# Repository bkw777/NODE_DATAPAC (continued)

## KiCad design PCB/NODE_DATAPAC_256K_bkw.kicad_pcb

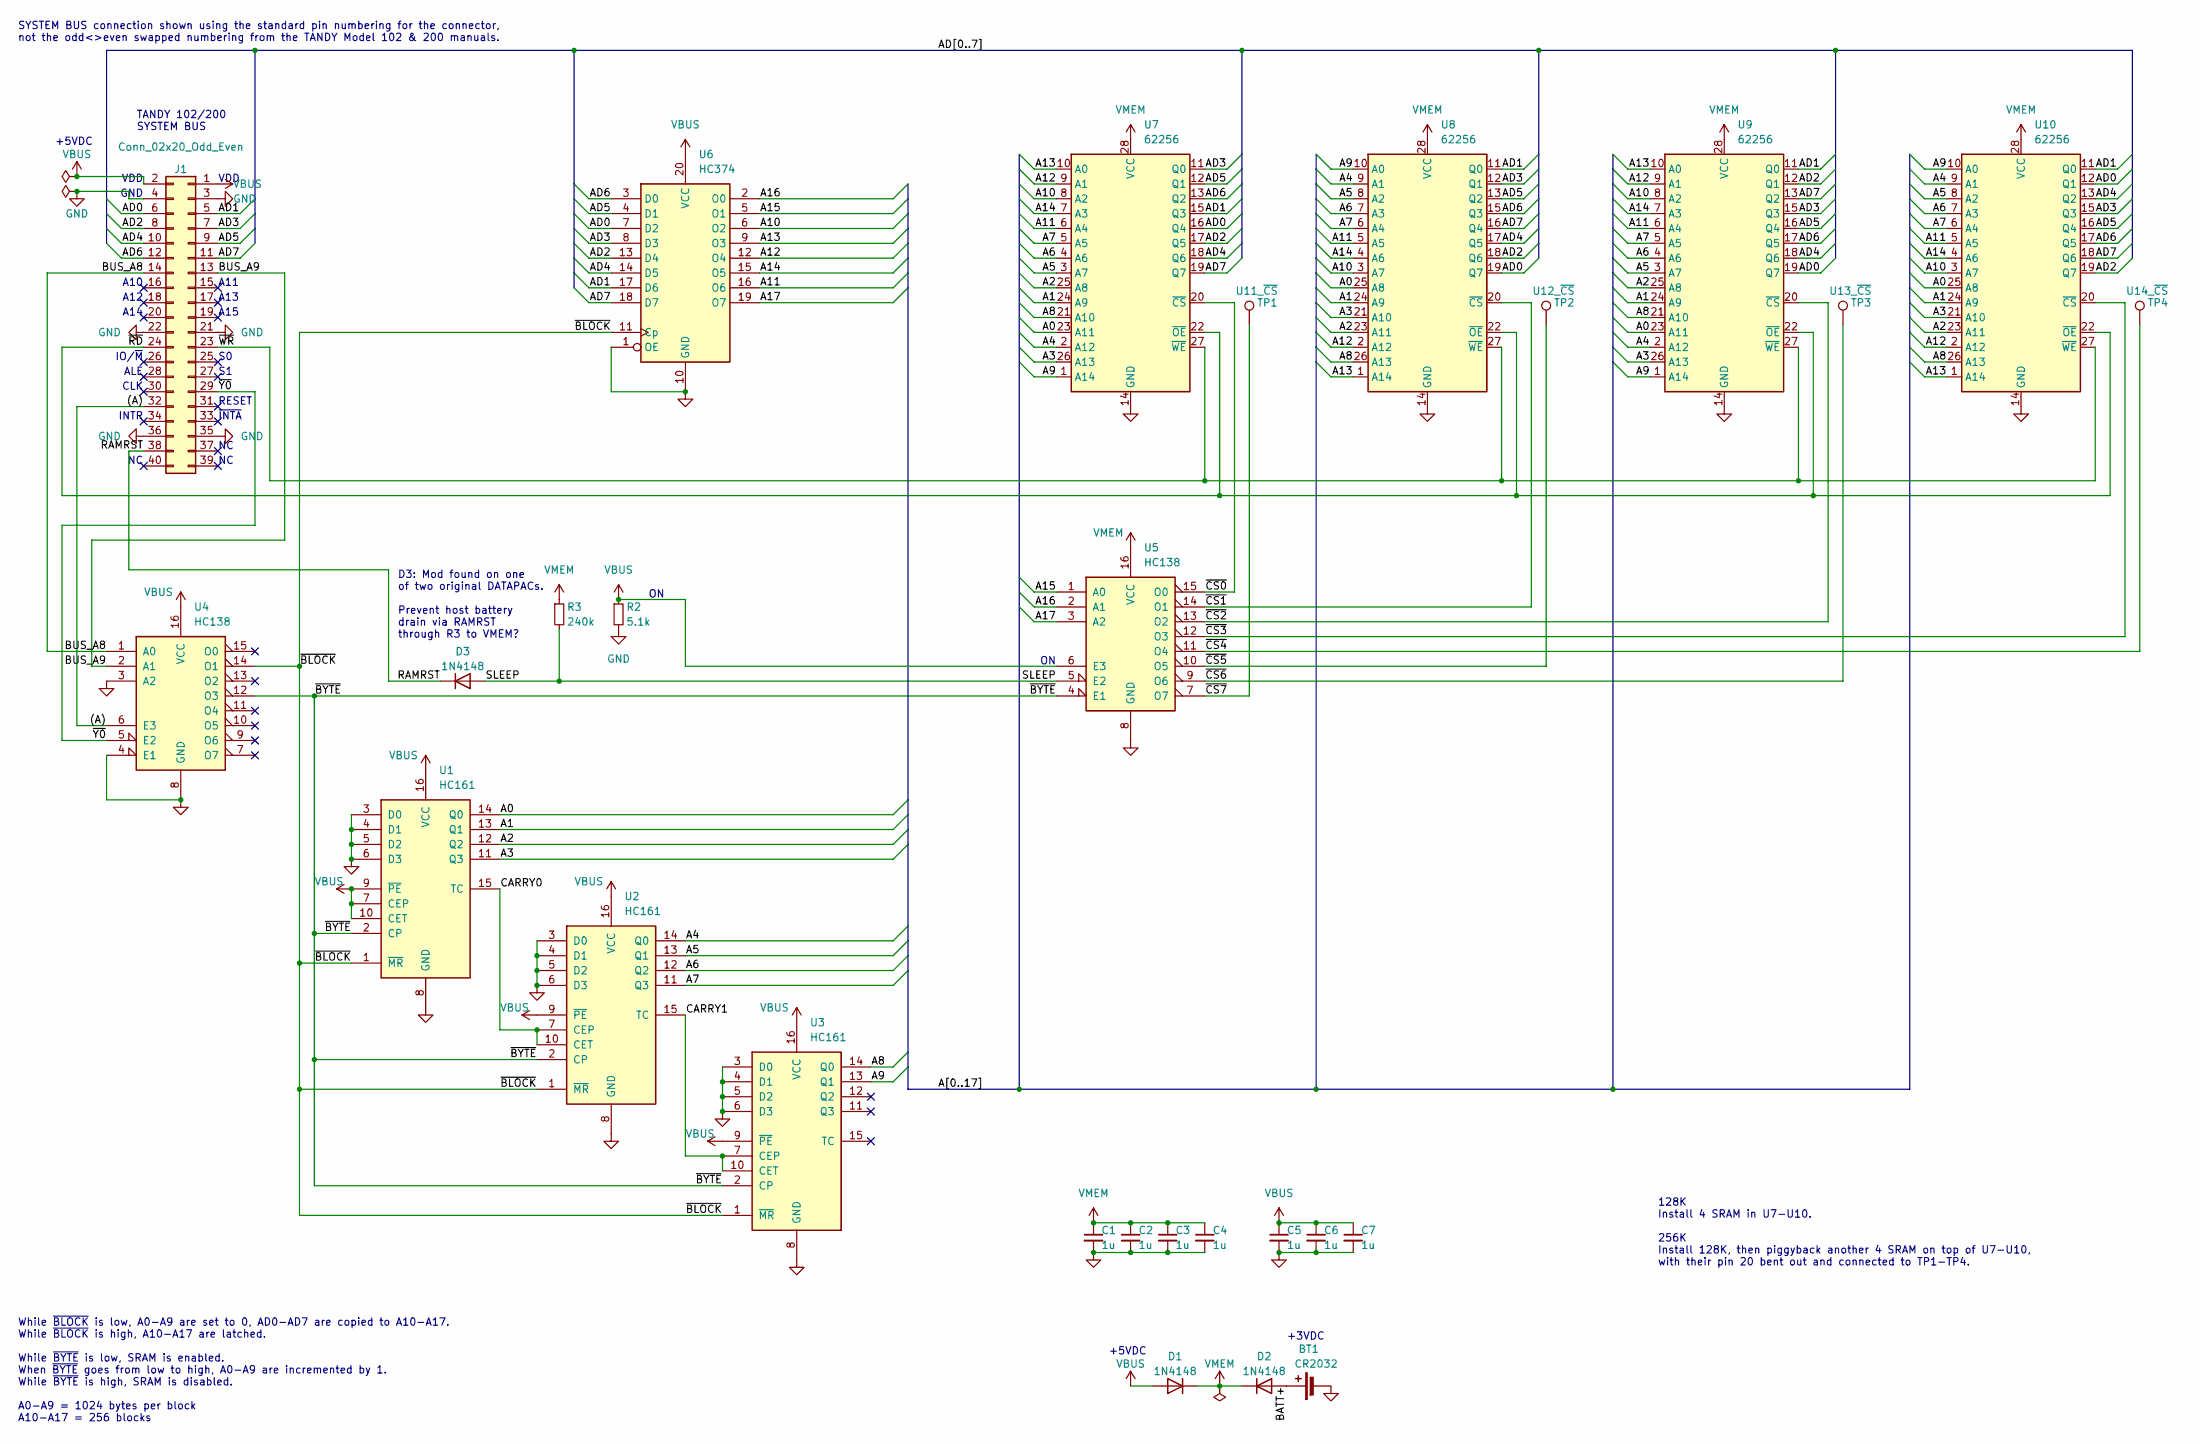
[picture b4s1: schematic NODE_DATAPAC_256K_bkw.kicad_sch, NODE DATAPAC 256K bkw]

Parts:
BT1: CR2032; BH-25x-x
C1, C2, C3, C4, C5, C6, C7: 1u; C_cer_tht_p2.5
D1, D2, D3: 1N4148; D_DO-35_SOD27_P10.16mm_Horizontal
J1: Conn_02x20_Odd_Even; IDC_to_board_2x20
R2: 5.1k; R_Axial_DIN0207_L6.3mm_D2.5mm_P10.16mm_Horizontal
R3: 240k; R_Axial_DIN0207_L6.3mm_D2.5mm_P10.16mm_Horizontal
TP1: U11_~{CS}; TP_THT
TP2: U12_~{CS}; TP_THT
TP3: U13_~{CS}; TP_THT
TP4: U14_~{CS}; TP_THT
U1, U2, U3: HC161; DIP-16_W7.62mm
U4, U5: HC138; DIP-16_W7.62mm
U6: HC374; DIP-20_W7.62mm
U7, U8, U9, U10: 62256; DIP-28_W15.24mm

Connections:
/(A): J1.32, U4.6 (E3)
/A0: U1.14 (Q0), U7.23 (A11), U8.25 (A8), U9.23 (A11), U10.25 (A8)
/A1: U1.13 (Q1), U7.24 (A9), U8.24 (A9), U9.24 (A9), U10.24 (A9)
/A2: U1.12 (Q2), U7.25 (A8), U8.23 (A11), U9.25 (A8), U10.23 (A11)
/A3: U1.11 (Q3), U7.26 (A13), U8.21 (A10), U9.26 (A13), U10.21 (A10)
/A4: U2.14 (Q0), U7.2 (A12), U8.9 (A1), U9.2 (A12), U10.9 (A1)
/A5: U2.13 (Q1), U7.3 (A7), U8.8 (A2), U9.3 (A7), U10.8 (A2)
/A6: U2.12 (Q2), U7.4 (A6), U8.7 (A3), U9.4 (A6), U10.7 (A3)
/A7: U2.11 (Q3), U7.5 (A5), U8.6 (A4), U9.5 (A5), U10.6 (A4)
/A8: U3.14 (Q0), U7.21 (A10), U8.26 (A13), U9.21 (A10), U10.26 (A13)
/A9: U3.13 (Q1), U7.1 (A14), U8.10 (A0), U9.1 (A14), U10.10 (A0)
/A10: U6.6 (O2), U7.8 (A2), U8.3 (A7), U9.8 (A2), U10.3 (A7)
/A11: U6.16 (O6), U7.6 (A4), U8.5 (A5), U9.6 (A4), U10.5 (A5)
/A12: U6.12 (O4), U7.9 (A1), U8.2 (A12), U9.9 (A1), U10.2 (A12)
/A13: U6.9 (O3), U7.10 (A0), U8.1 (A14), U9.10 (A0), U10.1 (A14)
/A14: U6.15 (O5), U7.7 (A3), U8.4 (A6), U9.7 (A3), U10.4 (A6)
/A15: U5.1 (A0), U6.5 (O1)
/A16: U5.2 (A1), U6.2 (O0)
/A17: U5.3 (A2), U6.19 (O7)
/AD0: J1.6, U6.7 (D2), U7.16 (Q4), U8.19 (Q7), U9.19 (Q7), U10.12 (Q1)
/AD1: J1.5, U6.17 (D6), U7.15 (Q3), U8.11 (Q0), U9.11 (Q0), U10.11 (Q0)
/AD2: J1.8, U6.13 (D4), U7.17 (Q5), U8.18 (Q6), U9.12 (Q1), U10.19 (Q7)
/AD3: J1.7, U6.8 (D3), U7.11 (Q0), U8.12 (Q1), U9.15 (Q3), U10.15 (Q3)
/AD4: J1.10, U6.14 (D5), U7.18 (Q6), U8.17 (Q5), U9.18 (Q6), U10.13 (Q2)
/AD5: J1.9, U6.4 (D1), U7.12 (Q1), U8.13 (Q2), U9.16 (Q4), U10.16 (Q4)
/AD6: J1.12, U6.3 (D0), U7.13 (Q2), U8.15 (Q3), U9.17 (Q5), U10.17 (Q5)
/AD7: J1.11, U6.18 (D7), U7.19 (Q7), U8.16 (Q4), U9.13 (Q2), U10.18 (Q6)
/BATT+: BT1.1 (+), D2.2 (A)
/BUS_A8: J1.14, U4.1 (A0)
/BUS_A9: J1.13, U4.2 (A1)
/CARRY0: U1.15 (TC), U2.7 (CEP), U2.10 (CET)
/CARRY1: U2.15 (TC), U3.7 (CEP), U3.10 (CET)
/RAMRST: D3.1 (K), J1.38
/SLEEP: D3.2 (A), R3.2, U5.5 (E2)
/~BLOCK: U1.1 (~MR), U2.1 (~MR), U3.1 (~MR), U4.14 (O1), U6.11 (Cp)
/~BYTE: U1.2 (CP), U2.2 (CP), U3.2 (CP), U4.12 (O3), U5.4 (E1)
/~CS0: U5.15 (O0), U7.20 (~CS)
/~CS1: U5.14 (O1), U8.20 (~CS)
/~CS2: U5.13 (O2), U9.20 (~CS)
/~CS3: U5.12 (O3), U10.20 (~CS)
/~CS4: TP4.1, U5.11 (O4)
/~CS5: TP2.1, U5.10 (O5)
/~CS6: TP3.1, U5.9 (O6)
/~CS7: TP1.1, U5.7 (O7)
/~RD: J1.24, U7.22 (~OE), U8.22 (~OE), U9.22 (~OE), U10.22 (~OE)
/~WR: J1.23, U7.27 (~WE), U8.27 (~WE), U9.27 (~WE), U10.27 (~WE)
/~Y0: J1.29, U4.5 (E2)
GND: BT1.2 (-), C1.2, C2.2, C3.2, C4.2, C5.2, C6.2, C7.2, J1.3, J1.4, J1.21, J1.22, J1.35, J1.36, R2.2, U1.3 (D0), U1.4 (D1), U1.5 (D2), U1.6 (D3), U1.8 (GND), U2.3 (D0), U2.4 (D1), U2.5 (D2), U2.6 (D3), U2.8 (GND), U3.3 (D0), U3.4 (D1), U3.5 (D2), U3.6 (D3), U3.8 (GND), U4.3 (A2), U4.4 (E1), U4.8 (GND), U5.8 (GND), U6.1 (OE), U6.10 (GND), U7.14 (GND), U8.14 (GND), U9.14 (GND), U10.14 (GND); also elsewhere on the board
VBUS: C5.1, C6.1, C7.1, D1.2 (A), J1.1, J1.2, R2.1, U1.7 (CEP), U1.9 (~PE), U1.10 (CET), U1.16 (VCC), U2.9 (~PE), U2.16 (VCC), U3.9 (~PE), U3.16 (VCC), U4.16 (VCC), U5.6 (E3), U6.20 (VCC)
VMEM: C1.1, C2.1, C3.1, C4.1, D1.1 (K), D2.1 (K), R3.1, U5.16 (VCC), U7.28 (VCC), U8.28 (VCC), U9.28 (VCC), U10.28 (VCC)

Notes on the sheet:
SYSTEM BUS connection shown using the standard pin numbering for the connector, not the odd<>even swapped numbering from the TANDY Model 102 & 200 manuals.
TANDY 102/200 SYSTEM BUS
+5VDC
A15
INTR
A14
ALE
~{INTA}
CLK
GND
IO/~{M}
D3: Mod found on one of two original DATAPACs. Prevent host battery drain via RAMRST through R3 to VMEM?
VDD
A10
RESET
+3VDC
While ~{BLOCK} is low, A0-A9 are set to 0, AD0-AD7 are copied to A10-A17. While ~{BLOCK} is high, A10-A17 are latched. While ~{BYTE} is low, SRAM is enabled. When ~{BYTE} goes from low to high, A0-A9 are incremented by 1. While ~{BYTE} is high, SRAM is disabled. A0-A9 = 1024 bytes per block A10-A17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
A11
128K Install 4 SRAM in U7-U10. 256K Install 128K, then piggyback another 4 SRAM on top of U7-U10, with their pin 20 bent out and connected to TP1-TP4.
A13
A12

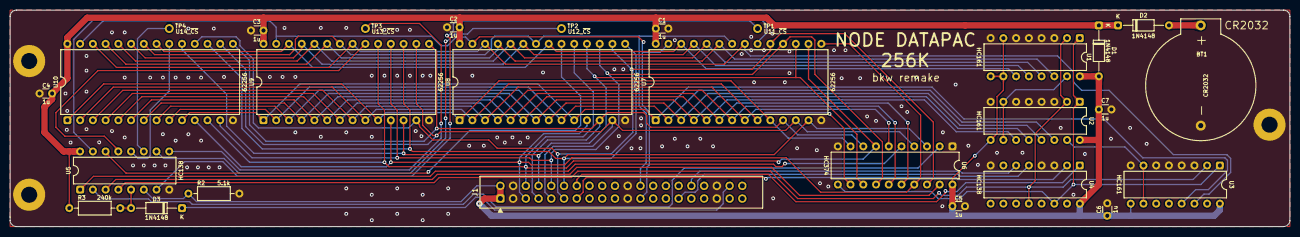
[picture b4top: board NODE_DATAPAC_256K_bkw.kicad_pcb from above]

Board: 2 copper layers, 255.3 x 43.2 mm, 31 parts (0 on the bottom side), 50 nets.

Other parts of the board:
H1, H2, H3: MountHole; MountingHole_3.2mm_M3_Pad

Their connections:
GND: H1.1, H2.1, H3.1; also elsewhere on the board

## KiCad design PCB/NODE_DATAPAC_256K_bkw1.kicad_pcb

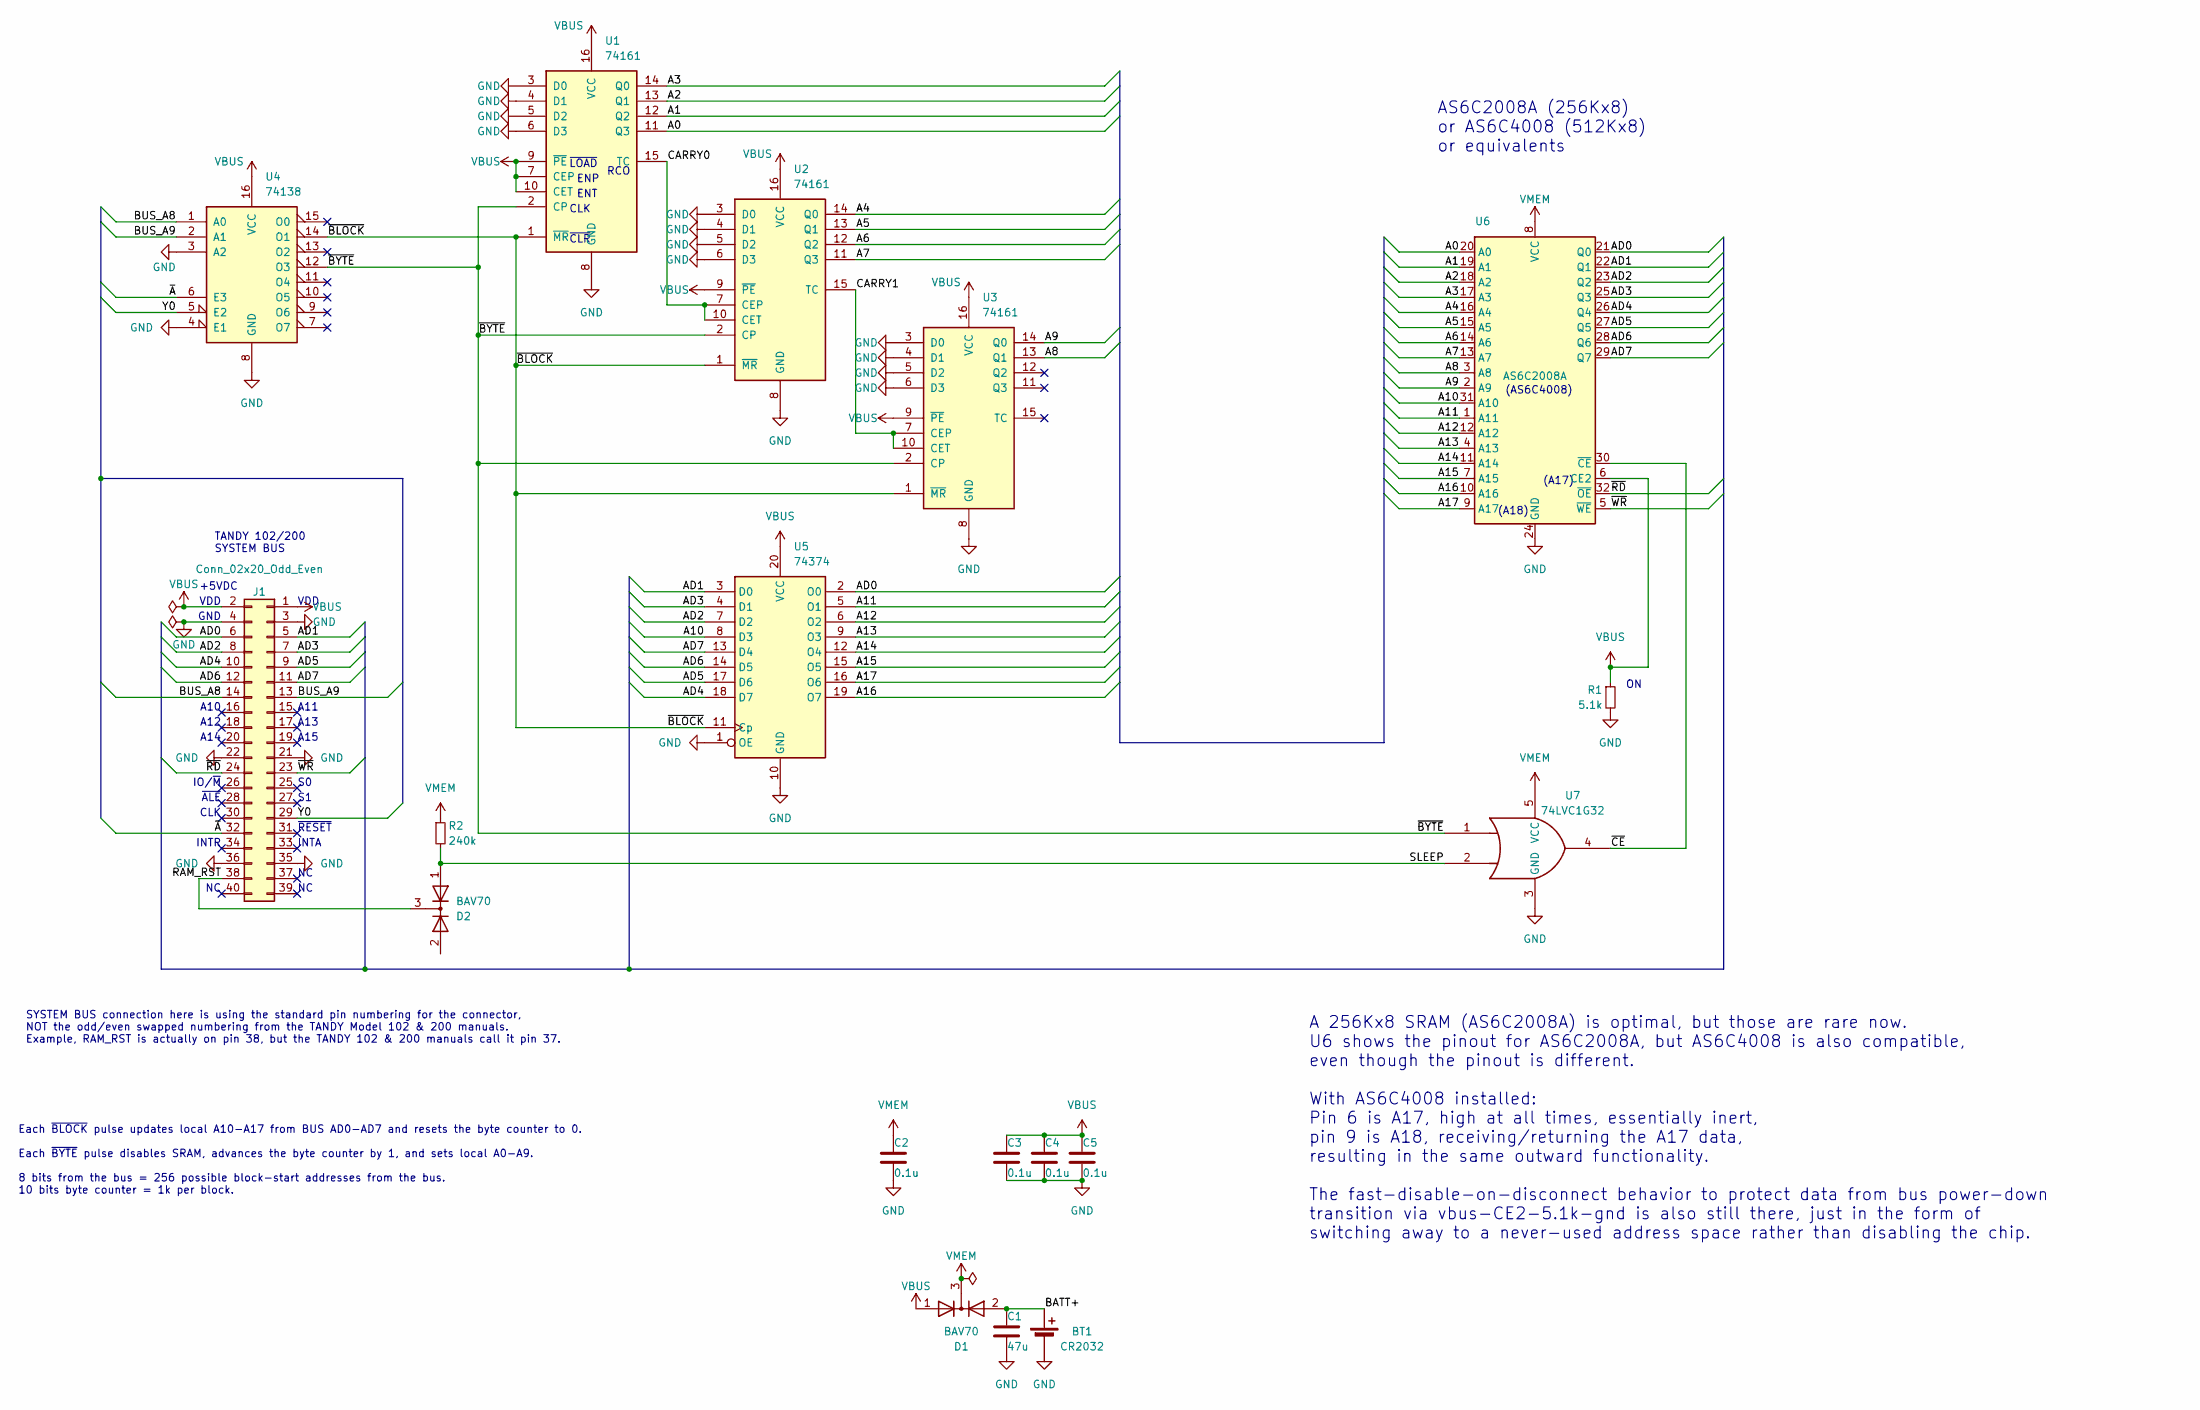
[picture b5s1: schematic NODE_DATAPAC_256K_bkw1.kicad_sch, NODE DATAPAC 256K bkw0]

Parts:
BT1: CR2032; BatteryHolder_Keystone_3034_1x20mm
C1: 47u; C_1206
C2, C3, C4, C5: 0.1u; C_0805
D1, D2: BAV70; SOT-23
J1: Conn_02x20_Odd_Even; IDC-Header_2x20_P2.54mm_Vertical
R1: 5.1k; R_0805
R2: 240k; R_0805
U1, U2, U3: 74161; TSSOP-16
U4: 74138; TSSOP-16
U5: 74374; TSSOP-20
U6: AS6C2008A; TSOP32-dual
U7: 74LVC1G32; SOT-353_SC-70-5

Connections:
/A0: U1.11 (Q3), U6.20 (A0)
/A1: U1.12 (Q2), U6.19 (A1)
/A2: U1.13 (Q1), U6.18 (A2)
/A3: U1.14 (Q0), U6.17 (A3)
/A4: U2.14 (Q0), U6.16 (A4)
/A5: U2.13 (Q1), U6.15 (A5)
/A6: U2.12 (Q2), U6.14 (A6)
/A7: U2.11 (Q3), U6.13 (A7)
/A8: U3.13 (Q1), U6.3 (A8)
/A9: U3.14 (Q0), U6.2 (A9)
/A10: U5.8 (D3), U6.31 (A10)
/A11: U5.5 (O1), U6.1 (A11)
/A12: U5.6 (O2), U6.12 (A12)
/A13: U5.9 (O3), U6.4 (A13)
/A14: U5.12 (O4), U6.11 (A14)
/A15: U5.15 (O5), U6.7 (A15)
/A16: U5.19 (O7), U6.10 (A16)
/A17: U5.16 (O6), U6.9 (A17)
/AD0: J1.6, U5.2 (O0), U6.21 (Q0)
/AD1: J1.5, U5.3 (D0), U6.22 (Q1)
/AD2: J1.8, U5.7 (D2), U6.23 (Q2)
/AD3: J1.7, U5.4 (D1), U6.25 (Q3)
/AD4: J1.10, U5.18 (D7), U6.26 (Q4)
/AD5: J1.9, U5.17 (D6), U6.27 (Q5)
/AD6: J1.12, U5.14 (D5), U6.28 (Q6)
/AD7: J1.11, U5.13 (D4), U6.29 (Q7)
/BATT+: BT1.1 (+), C1.1, D1.2 (A)
/BUS_A8: J1.14, U4.1 (A0)
/BUS_A9: J1.13, U4.2 (A1)
/CARRY0: U1.15 (TC), U2.7 (CEP), U2.10 (CET)
/CARRY1: U2.15 (TC), U3.7 (CEP), U3.10 (CET)
/RAM_RST: D2.3 (K), J1.38
/SLEEP: D2.1 (A), R2.2, U7.2
/Y0: J1.29, U4.5 (E2)
/~A: J1.32, U4.6 (E3)
/~BLOCK: U1.1 (~MR), U2.1 (~MR), U3.1 (~MR), U4.14 (O1), U5.11 (Cp)
/~BYTE: U1.2 (CP), U2.2 (CP), U3.2 (CP), U4.12 (O3), U7.1
/~CE: U6.30 (~CE), U7.4
/~RD: J1.24, U6.32 (~OE)
/~WR: J1.23, U6.5 (~WE)
GND: BT1.2 (-), C1.2, C2.2, C3.2, C4.2, C5.2, J1.3, J1.4, J1.21, J1.22, J1.35, J1.36, R1.2, U1.3 (D0), U1.4 (D1), U1.5 (D2), U1.6 (D3), U1.8 (GND), U2.3 (D0), U2.4 (D1), U2.5 (D2), U2.6 (D3), U2.8 (GND), U3.3 (D0), U3.4 (D1), U3.5 (D2), U3.6 (D3), U3.8 (GND), U4.3 (A2), U4.4 (E1), U4.8 (GND), U5.1 (OE), U5.10 (GND), U6.24 (GND), U7.3 (GND)
VBUS: C3.1, C4.1, C5.1, D1.1 (A), J1.1, J1.2, R1.1, U1.7 (CEP), U1.9 (~PE), U1.10 (CET), U1.16 (VCC), U2.9 (~PE), U2.16 (VCC), U3.9 (~PE), U3.16 (VCC), U4.16 (VCC), U5.20 (VCC), U6.6 (CE2)
VMEM: C2.1, D1.3 (K), R2.1, U6.8 (VCC), U7.5 (VCC)

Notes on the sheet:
(A18)
SYSTEM BUS connection here is using the standard pin numbering for the connector, NOT the odd/even swapped numbering from the TANDY Model 102 & 200 manuals. Example, RAM_RST is actually on pin 38, but the TANDY 102 & 200 manuals call it pin 37.
TANDY 102/200 SYSTEM BUS
+5VDC
A15
INTR
A14
~{ALE}
~{CLR}
ENT
A 256Kx8 SRAM (AS6C2008A) is optimal, but those are rare now. U6 shows the pinout for AS6C2008A, but AS6C4008 is also compatible, even though the pinout is different. With AS6C4008 installed: Pin 6 is A17, high at all times, essentially inert, pin 9 is A18, receiving/returning the A17 data, resulti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
INTA
CLK
GND
IO/~{M}
VDD
A10
AS6C2008A (256Kx8) or AS6C4008 (512Kx8) or equivalents
(A17)
~{LOAD}
~{RESET}
Each ~{BLOCK} pulse updates local A10-A17 from BUS AD0-AD7 and resets the byte counter to 0. Each ~{BYTE} pulse disables SRAM, advances the byte counter by 1, and sets local A0-A9. 8 bits from the bus = 256 possible block-start addresses from the bus. 10 bits byte counter = 1k per block.
ENP
A11
RCO
A13
(AS6C4008)
A12

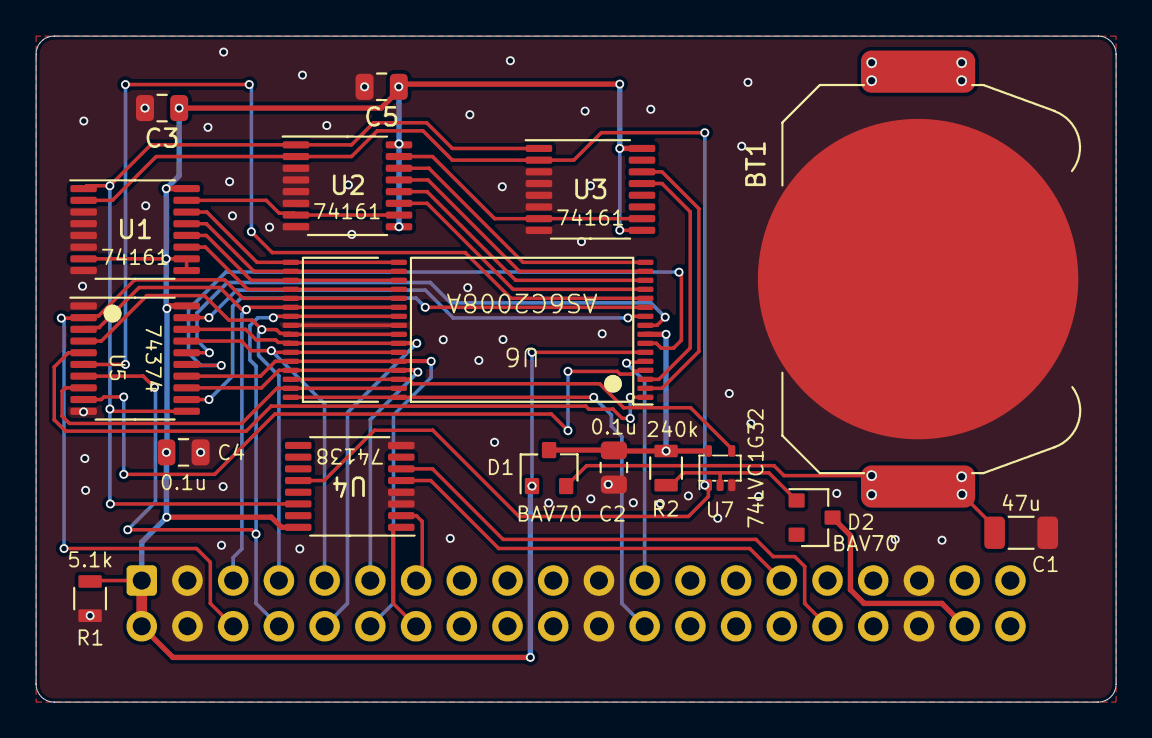
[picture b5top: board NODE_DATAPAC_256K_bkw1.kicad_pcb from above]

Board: 2 copper layers, 60.0 x 37.0 mm, 18 parts (1 on the bottom side), 43 nets.
